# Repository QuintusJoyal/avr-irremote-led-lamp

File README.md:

# AVR IR remote LED lamp

This project implements an infrared (IR) remote-controlled LED system using an AVR microcontroller. It allows users to adjust LED brightness and toggle RGB LED colors using a compatible IR remote control.

## Features

- Adjust RGB LED colors with volume up and down commands.
- Control LED brightness with channel up and down commands.
- Turn off all LEDs with the power command.
- Smooth LED dimming achieved through software PWM.

## Hardware Requirements

- AVR microcontroller (e.g., ATmega328P or Arduino uno)
- 1x IR receiver (VS1838B)
- 5x LEDs
  - 4x single-color
  - 1x RKGB
- 7x 330 Ohms resistors
- 1x IR remote control
- 1x Power supply (9V)
---
>For PCB
>- 2x 20pf ceramic capacitors
>- 2x 10uf 50V electrolytic capacitor
>- 1x 16Mhz crystal osclilator
>- 1x 100 Ohms resistors
>- 2x 10k Ohms resistors
>- 1x PCB mount DC jack
>- 1x 28 pin IC socket
>- 1x 1x5 Female header SIL
>- 1x 7805 5V voltage regulator
>- 1x ATMEGA328P IC
---
## Diagram
||
|:--:|
|Prototype|
||
||
|PCB|
||
||
|Pinout|
||
||
## Software Requirements

- AVR-GCC toolchain
- AVRDUDE (for flashing the microcontroller)
- Required AVR libraries (included in the [`./src/libs`](./src/libs) directory)
  - [IRremote.h](./src/libs/IRremote.h)
  - [softwarePWM.h](./src/libs/softwarePWM.h)
  - [uart.h](./src/libs/uart.h) (Optional)

## Installation

1. Connect the hardware components according to the schematic.
2. Clone this repository to your local machine.
3. Compile the source code using the AVR-GCC toolchain.
```bash
make all
```
4. Flash the compiled binary onto the AVR microcontroller using AVRDUDE.
```bash
make flash
```
---
>Build the docker image for easy toolchain deployment
>1. Build the image
>```
>docker build -f Dockerfile -t avr-dev .
>```
>2. Run the container
>```
>docker run --rm -it --name avr-dev --device=/dev/ttyACM0 avr-dev
>```
>3. Flash
>```
>make flash
>```
---
## Usage

1. Power on the system.
2. Point the IR remote control towards the IR receiver module.
3. Press the appropriate buttons on the remote control to control the LEDs:
   - Volume up/down: Change RGB LED colors.
   - Channel up/down: Adjust LED brightness.
   - Power: Turn off all LEDs.
4. LED status updates will be displayed via UART communication (if needed).

## Notes
- Uncomment uart if needed.
- You may need to change command codes according to your IR remote, use uart to find your codes.
- Changing ports have to be changed in [softwarePWM.h](./src/libs/softwarePWM.h)'s channel sections.

## References
- [IRremote.h](https://www.programming-electronics-diy.xyz/2022/08/ir-remote-control-library-for-avr.html) - Liviu Istrate
- [softwarePWM.h](https://www.programming-electronics-diy.xyz/2021/02/multi-channel-software-pwm-library-for.html) - Liviu Istrate

## Contributions

Contributions are welcome! Feel free to submit bug reports, feature requests, or pull requests.

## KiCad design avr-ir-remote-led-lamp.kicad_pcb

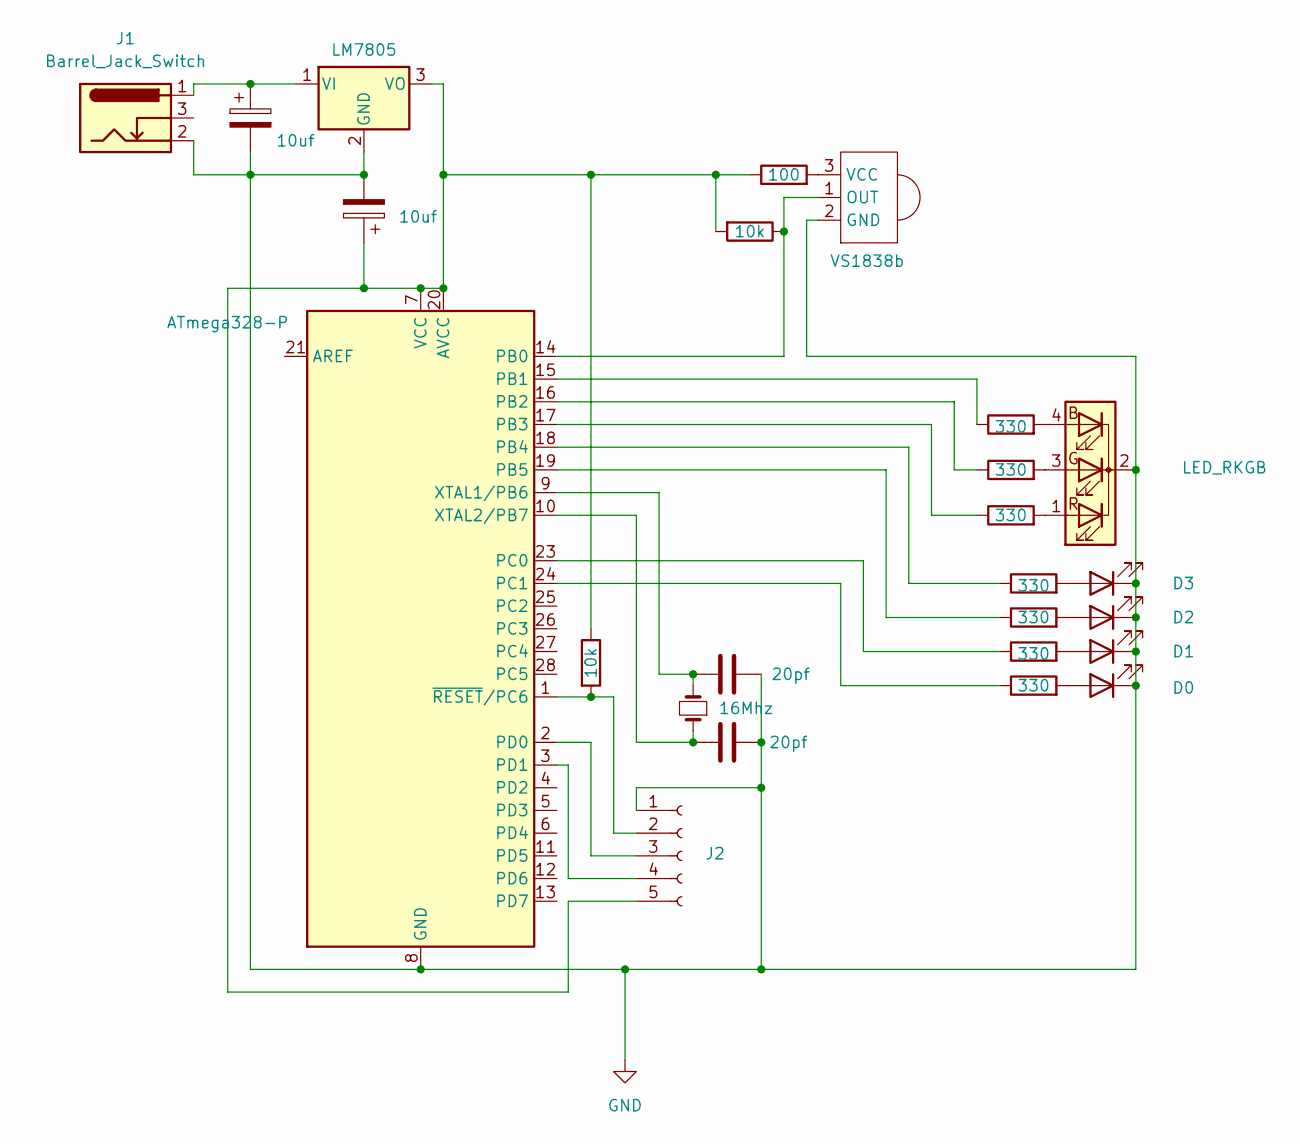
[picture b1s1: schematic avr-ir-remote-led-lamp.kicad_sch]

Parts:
C1, C3: 10uf; CP_Radial_D6.3mm_P2.50mm
C2, C4: 20pf; C_Disc_D3.0mm_W1.6mm_P2.50mm
D0, D1, D2, D3: LED; LED_D5.0mm_Clear
D5: LED_RKGB; LED_D5.0mm-4_RGB
IR1: VS1838b
J1: Barrel_Jack_Switch; BarrelJack_Horizontal
J2: Conn_01x05_Socket; PinSocket_1x05_P2.54mm_Vertical
R1, R2, R3, R4, R5, R6, R7: 330; R_Axial_DIN0207_L6.3mm_D2.5mm_P10.16mm_Horizontal
R8: 100; R_Axial_DIN0207_L6.3mm_D2.5mm_P10.16mm_Horizontal
R9, R10: 10k; R_Axial_DIN0207_L6.3mm_D2.5mm_P10.16mm_Horizontal
U1: ATmega328-P; DIP-28_W7.62mm
U2: LM7805; TO-220-3_Vertical
Y1: 16Mhz; Crystal_HC18-U_Vertical

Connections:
GND: C1.2, C2.2, C3.2, C4.2, D0.1 (K), D1.1 (K), D2.1 (K), D3.1 (K), D5.2 (K), IR1.2 (GND), J1.2, J2.1, U1.8 (GND), U1.22 (GND), U2.2 (GND)
unnamed: D0.2 (A), R1.2
unnamed: D1.2 (A), R2.2
unnamed: D2.2 (A), R3.2
unnamed: D3.2 (A), R4.2
unnamed: D5.4 (BA), R5.2
unnamed: D5.3 (GA), R6.2
unnamed: D5.1 (RA), R7.2
unnamed: IR1.1 (OUT), R9.1, U1.14 (PB0)
unnamed: IR1.3 (VCC), R8.2
unnamed: J2.2, R10.2, U1.1 (~RESET/PC6)
unnamed: J2.3, U1.2 (PD0)
unnamed: J2.4, U1.3 (PD1)
unnamed: C1.1, J2.5, R8.1, R9.2, R10.1, U1.7 (VCC), U1.20 (AVCC), U2.3 (VO)
unnamed: R5.1, U1.15 (PB1)
unnamed: R6.1, U1.16 (PB2)
unnamed: R7.1, U1.17 (PB3)
unnamed: R4.1, U1.18 (PB4)
unnamed: R3.1, U1.19 (PB5)
unnamed: R2.1, U1.23 (PC0)
unnamed: R1.1, U1.24 (PC1)
unnamed: C4.1, U1.9 (XTAL1/PB6), Y1.2
unnamed: C2.1, U1.10 (XTAL2/PB7), Y1.1
unnamed: C3.1, J1.1, U2.1 (VI)

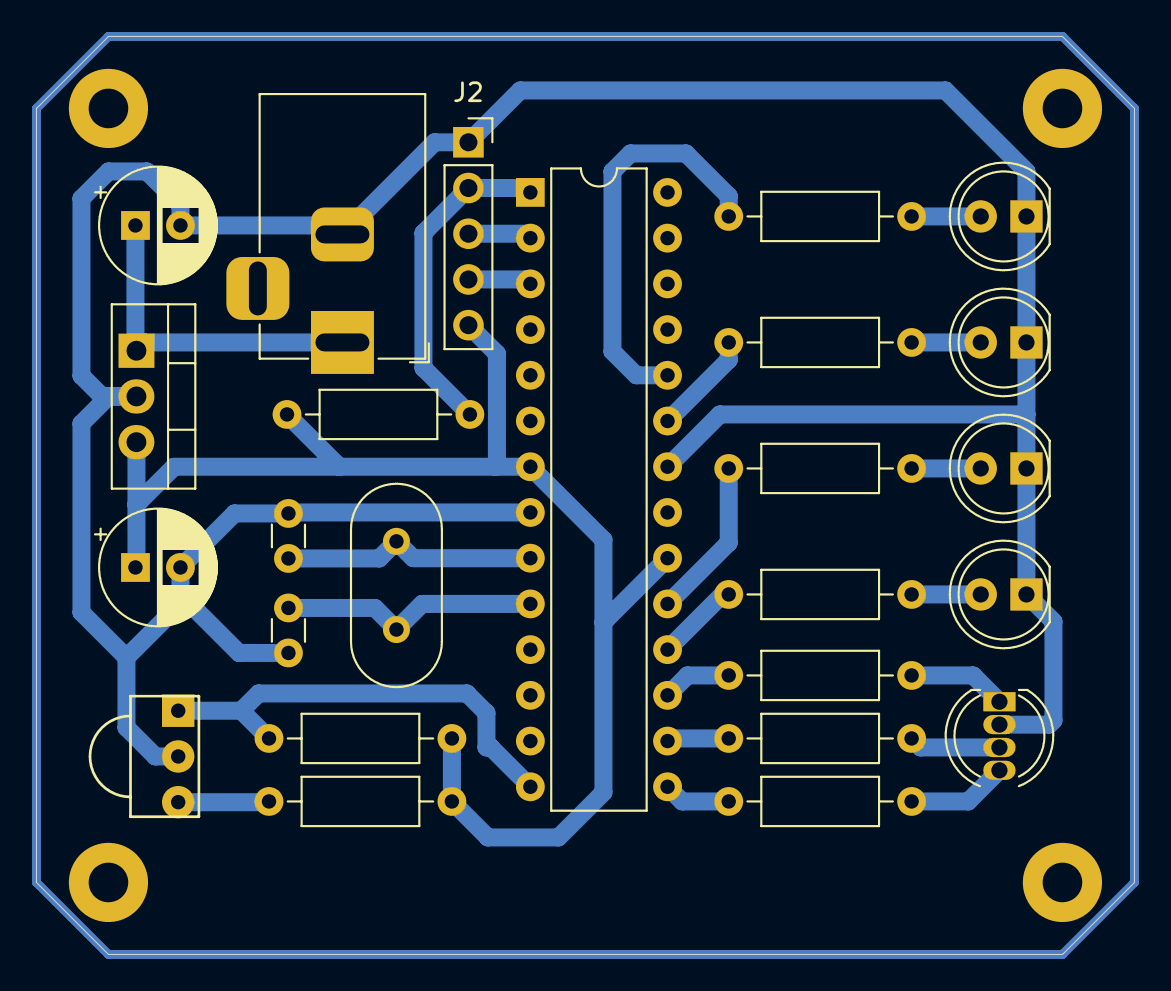
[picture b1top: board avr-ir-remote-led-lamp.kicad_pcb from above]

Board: 2 copper layers, 61.0 x 51.0 mm, 25 parts (0 on the bottom side), 24 nets.

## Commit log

2024-04-24 init
2024-05-04 added PCB design
2024-05-04 Docker file update
2024-05-04 Updated readme for Dockerfile
